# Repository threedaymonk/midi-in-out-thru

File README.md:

# MIDI In/Out/Thru

I wanted a MIDI interface for microcontrollers that would

- work on 3.3V,
- use full-size DIN connectors,
- include MIDI Thru, and
- have all the connectors in one line.

This achieves that. You can attach it to a Raspberry Pi to give MIDI in to
[MiniDexed](https://github.com/probonopd/MiniDexed) or to a Raspberry Pi Pico
to make a USB to MIDI interface with [MIDI adapter
code](https://github.com/rsta2/pico/tree/main/midi_adapter).

If you don't want activity LEDs, you can omit R1, R2, LED1, LED2.

It's also possible to adapt this to 5V by changing R1 and R2 to 330 ohms,
and R6, R7, R8 and R9 to 220 ohms.

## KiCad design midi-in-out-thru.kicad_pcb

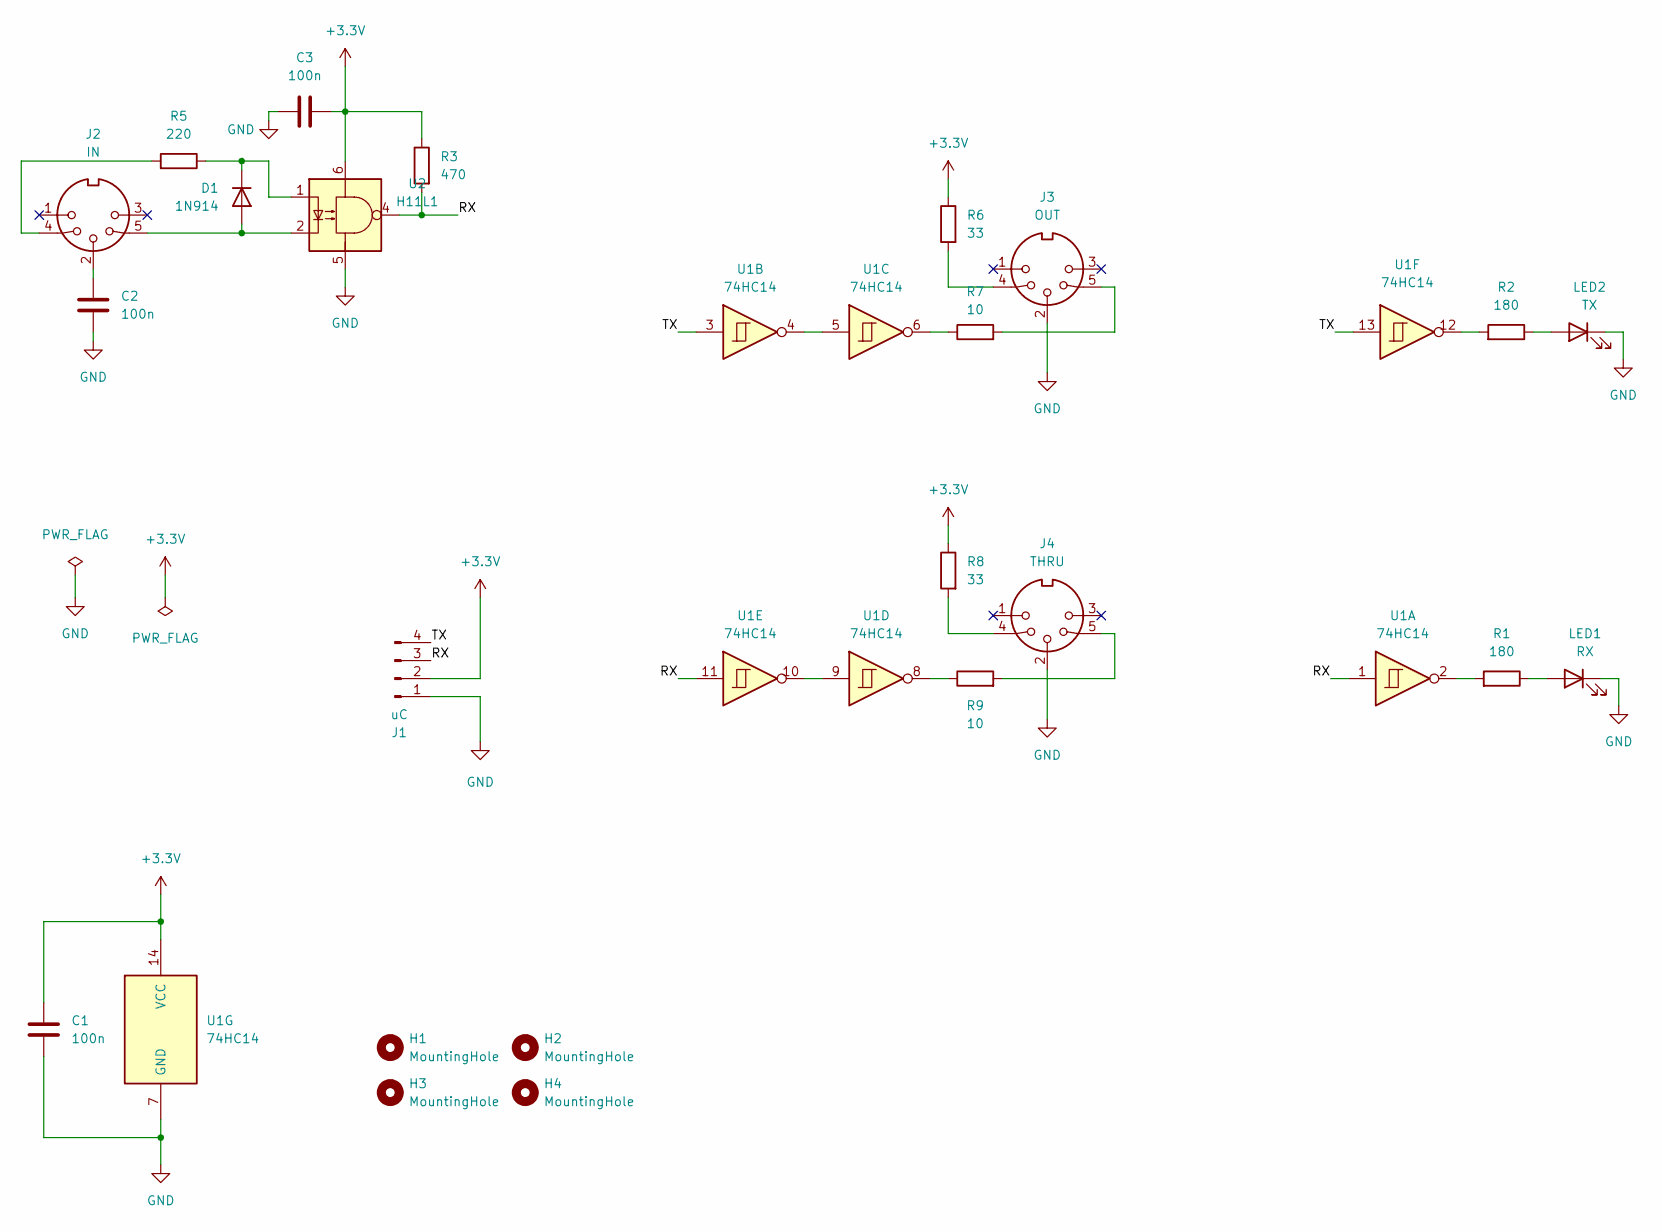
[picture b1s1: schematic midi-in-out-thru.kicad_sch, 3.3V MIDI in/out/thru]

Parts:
C1, C2, C3: 100n; C_Disc_D3.8mm_W2.6mm_P2.50mm
D1: 1N914; D_DO-35_SOD27_P7.62mm_Horizontal
H1, H2, H3, H4: MountingHole; MountingHole_3.2mm_M3
J1: uC; PinHeader_1x04_P2.54mm_Vertical
J2: IN; MIDI_DIN5
J3: OUT; MIDI_DIN5
J4: THRU; MIDI_DIN5
LED1: RX; LED_D3.0mm
LED2: TX; LED_D3.0mm
R1, R2: 180; R_Axial_DIN0204_L3.6mm_D1.6mm_P7.62mm_Horizontal
R3: 470; R_Axial_DIN0204_L3.6mm_D1.6mm_P7.62mm_Horizontal
R5: 220; R_Axial_DIN0204_L3.6mm_D1.6mm_P7.62mm_Horizontal
R6, R8: 33; R_Axial_DIN0204_L3.6mm_D1.6mm_P7.62mm_Horizontal
R7, R9: 10; R_Axial_DIN0204_L3.6mm_D1.6mm_P7.62mm_Horizontal
U1: 74HC14; DIP-14_W7.62mm
U2: H11L1; DIP-6_W7.62mm

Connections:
+3.3V: C1.1, C3.2, J1.2, R3.1, R6.1, R8.1, U1.14 (VCC), U2.6
/RX: J1.3, R3.2, U1.1, U1.11, U2.4
/TX: J1.4, U1.3, U1.13
GND: C1.2, C2.2, C3.1, J1.1, J3.2, J4.2, LED1.1 (K), LED2.1 (K), U1.7 (GND), U2.5
unnamed: C2.1, J2.2
unnamed: D1.1 (K), R5.1, U2.1
unnamed: D1.2 (A), J2.5, U2.2
unnamed: J2.4, R5.2
unnamed: J3.4, R6.2
unnamed: J3.5, R7.2
unnamed: J4.4, R8.2
unnamed: J4.5, R9.2
unnamed: LED1.2 (A), R1.1
unnamed: LED2.2 (A), R2.1
unnamed: R1.2, U1.2
unnamed: R2.2, U1.12
unnamed: R7.1, U1.6
unnamed: R9.1, U1.8
unnamed: U1.4, U1.5
unnamed: U1.9, U1.10

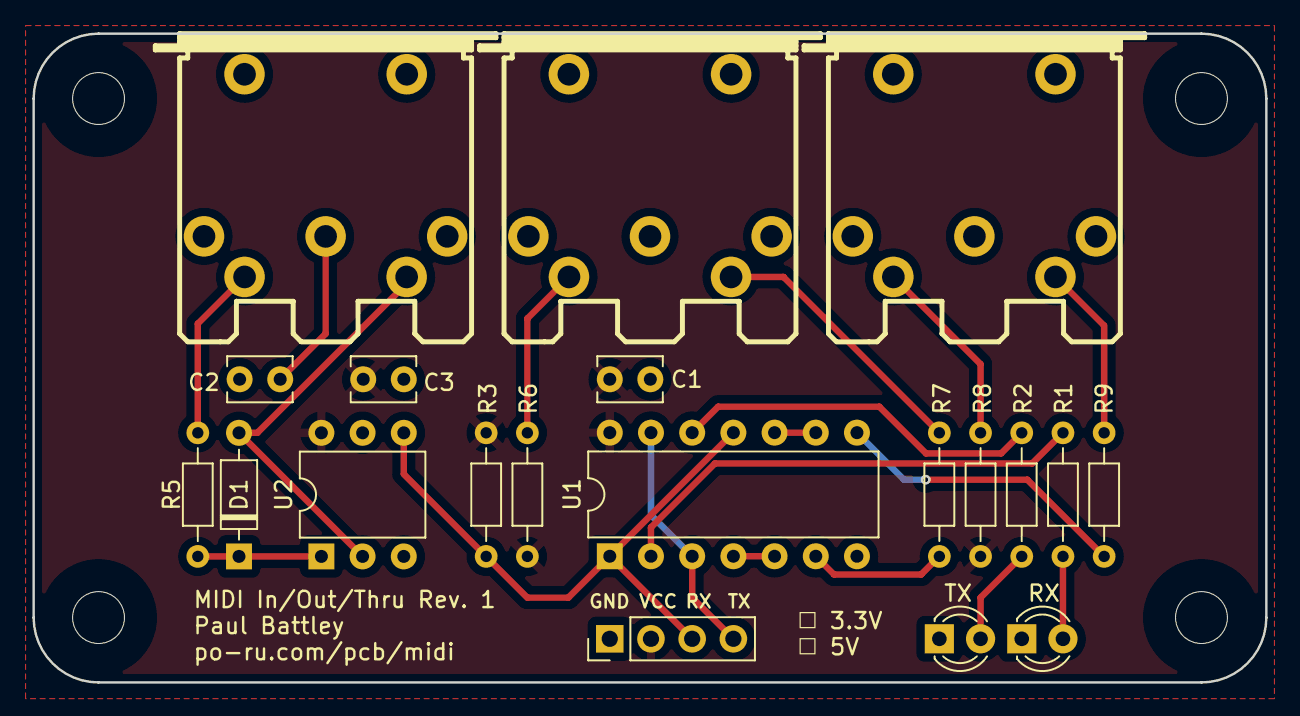
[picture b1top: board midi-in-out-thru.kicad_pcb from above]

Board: 2 copper layers, 76.0 x 40.0 mm, 24 parts (0 on the bottom side), 20 nets.

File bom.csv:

"Ref","Quantity","Value","Details"
"C1, C2, C3","3","100n","2.5mm pitch"
"D1","1","1N914",
"J1","1","1x4 pin header",
"J2, J3, J4","3","DIN5 180° socket","RS 491-087 or Multicomp PSG03463 or Deltron 671-0501"
"LED1","1","Green",
"LED2","1","Red",
"R1, R2","2","180","(or 220)"
"R3","1","470",
"R5","1","220",
"R6, R8","2","33",
"R7, R9","2","10",
"U1","1","74HC14",
"U2","1","H11L1",

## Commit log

2022-10-02 Initial empty commit
2022-10-02 Copy 6n138 circuit
2022-10-02 Use H11L1
    Resistor values taken from CA-033 Update 2014
2022-10-02 First PCB layout
2022-10-03 Completed initial layout
2022-10-16 Smaller resistors, neater layout
2022-10-16 Tweak tracks before rounding
2022-10-16 Remove extra layers
2022-10-30 Add LICENSE
2022-10-30 Ignore JLC files
2022-10-30 Add BOM
2022-10-30 Add README and photo
